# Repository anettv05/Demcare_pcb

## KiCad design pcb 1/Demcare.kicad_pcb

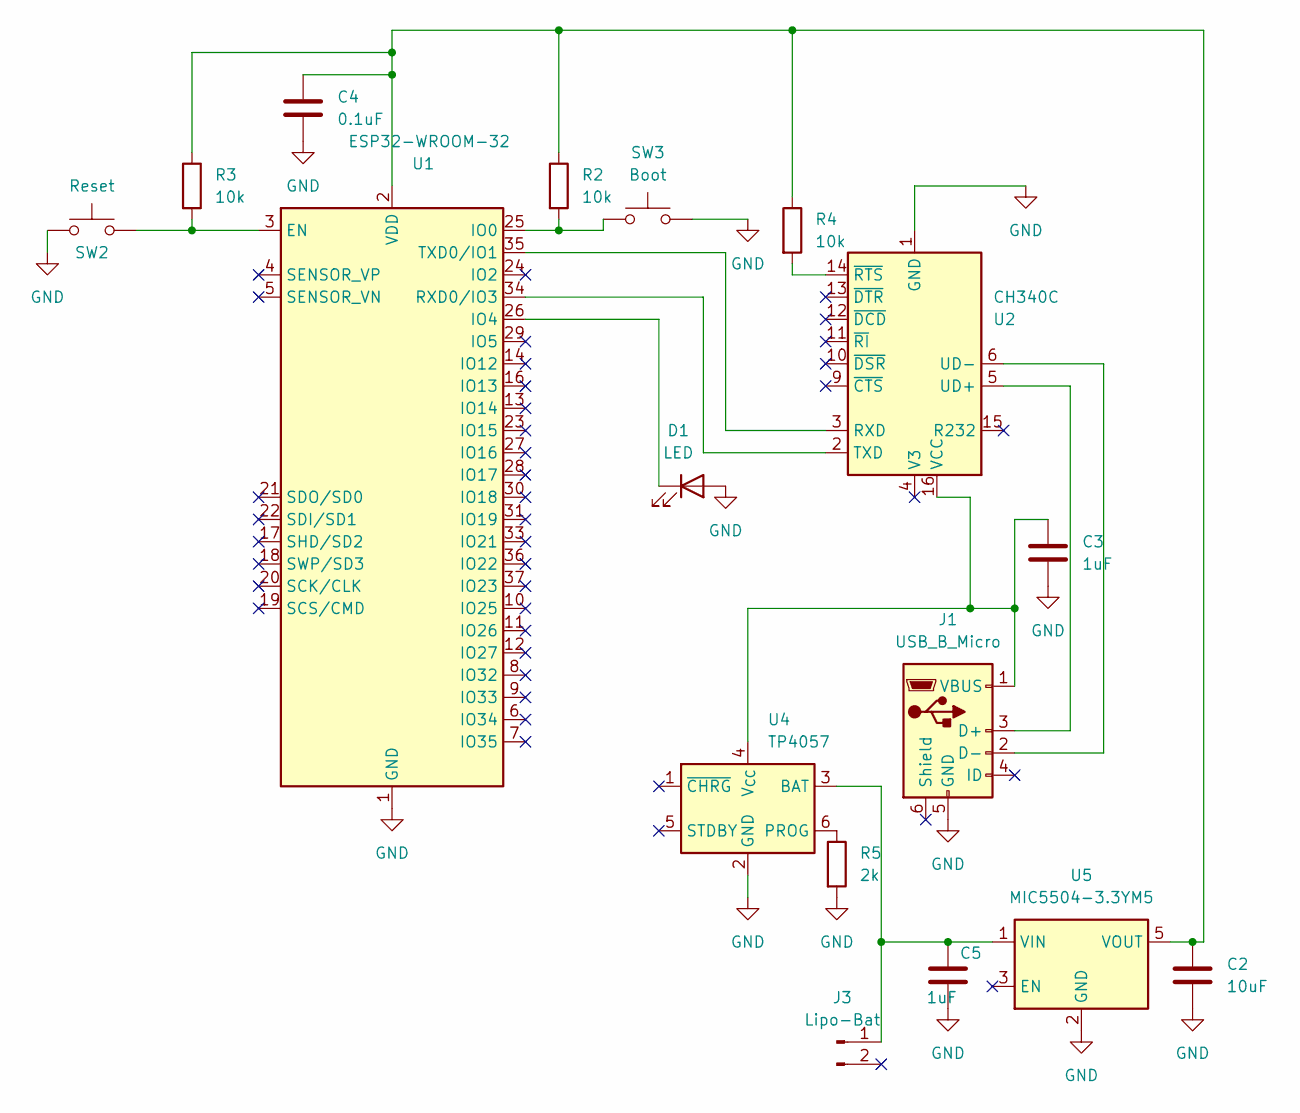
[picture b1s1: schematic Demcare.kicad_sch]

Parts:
C2: 10uF; C_0805_2012Metric
C3, C5: 1uF; C_0805_2012Metric
C4: 0.1uF; C_0805_2012Metric
D1: LED; LED_0805_2012Metric
J1: USB_B_Micro; USB_Micro-B_Amphenol_10103594-0001LF_Horizontal
J3: Lipo-Bat; JST_PH_S2B-PH-K_1x02_P2.00mm_Horizontal
R2, R3, R4: 10k; R_0201_0603Metric
R5: 2k; R_0201_0603Metric
SW2: Reset; SW_SPST_TL3342
SW3: Boot; SW_SPST_TL3342
U1: ESP32-WROOM-32
U2: CH340C; SOIC-16_3.9x9.9mm_P1.27mm
U4: TP4057; SOT-23-6
U5: MIC5504-3.3YM5; SOT-23-5

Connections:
GND: C2.2, C3.2, C4.2, C5.2, D1.2 (A), J1.5 (GND), R5.2, SW2.1, SW3.2, U1.1 (GND), U1.15 (GND), U1.38 (GND), U1.39 (GND), U2.1 (GND), U4.2 (GND), U5.2 (GND)
unnamed: D1.1 (K), U1.26 (IO4)
unnamed: J1.3 (D+), U2.5 (UD+)
unnamed: J1.2 (D-), U2.6 (UD-)
unnamed: C3.1, J1.1 (VBUS), U2.16 (VCC), U4.4 (V_{CC})
unnamed: C5.1, J3.1, U4.3 (BAT), U5.1 (VIN)
unnamed: R3.2, SW2.2, U1.3 (EN)
unnamed: R2.2, SW3.1, U1.25 (IO0)
unnamed: U1.34 (RXD0/IO3), U2.2 (TXD)
unnamed: U1.35 (TXD0/IO1), U2.3 (RXD)
unnamed: C2.1, C4.1, R2.1, R3.1, R4.1, U1.2 (VDD), U5.5 (VOUT)
unnamed: R4.2, U2.14 (~RTS)
unnamed: R5.1, U4.6 (PROG)

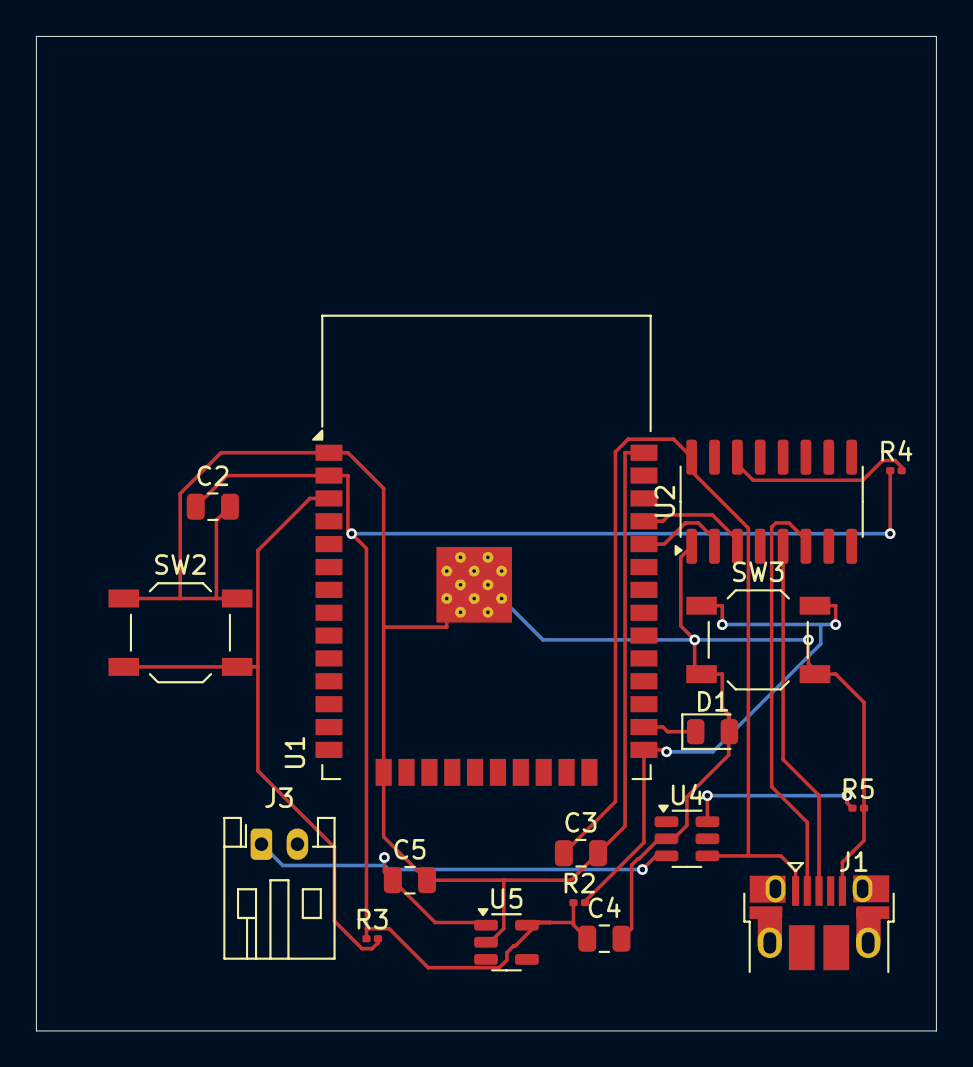
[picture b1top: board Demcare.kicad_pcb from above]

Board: 2 copper layers, 50.0 x 55.2 mm, 17 parts (0 on the bottom side), 13 nets.

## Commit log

2025-07-24 rerouted the pcb
